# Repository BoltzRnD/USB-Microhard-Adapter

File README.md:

# USB-Microhard-Adapter
 USB to RS232 with 12V Boost Converter for Microhard

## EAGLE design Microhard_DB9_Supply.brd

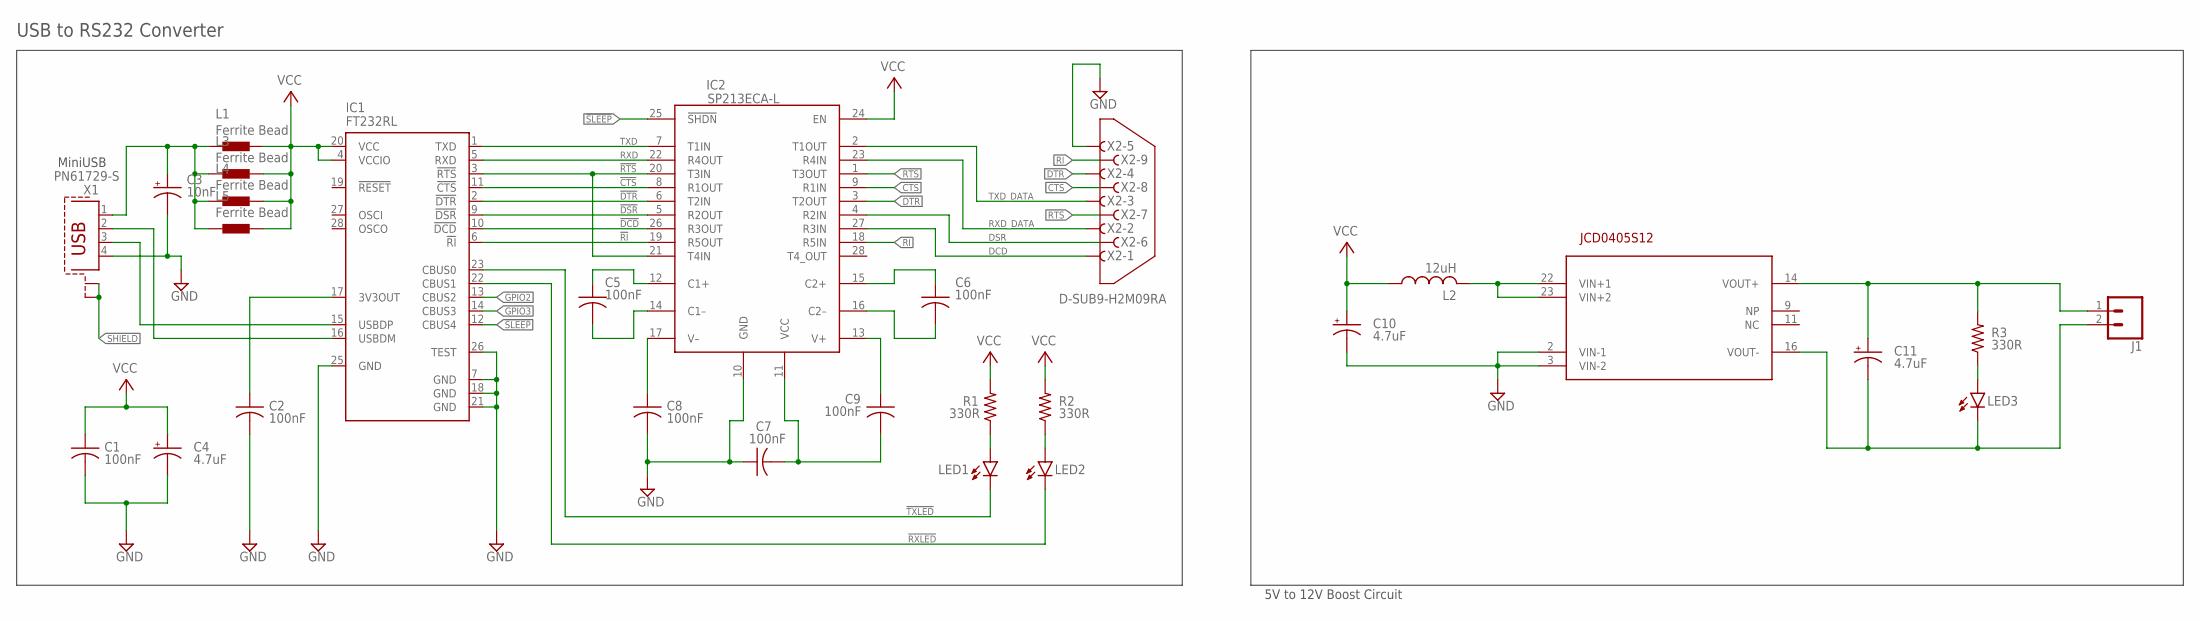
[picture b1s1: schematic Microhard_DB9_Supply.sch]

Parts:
C1, C2, C5, C6, C7, C8, C9: 100nF; C0402
C3: 10nF; PANASONIC_A
C4, C10, C11: 4.7uF; PANASONIC_D
IC1: FT232RL; SSOP28
IC2: SP213ECA-L; SSOP28
J1: CONN_02LOCK_LONGPADS; 1X02_LOCK_LONGPADS
L1, L3, L4, L5: Ferrite Bead; 0402
L2: 12uH; 0207/7
LED1, LED2, LED3: LEDCHIP-LED0603; CHIP-LED0603
R1, R2, R3: 330R; R0402
U$1: JCD0505S12JCD0505S12; DIP1524W53P254L3175H1040Q24A
X1: PN61729-S
X2: D-SUB9-H2M09RA; H2M09RA

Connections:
!CTS: IC1.11 (!CTS), IC2.8 (R1OUT)
!DCD: IC1.10 (!DCD), IC2.26 (R3OUT)
!DSR: IC1.9 (!DSR), IC2.5 (R2OUT)
!DTR: IC1.2 (!DTR), IC2.6 (T2IN)
!RI: IC1.6 (!RI), IC2.19 (R5OUT)
!RTS: IC1.3 (!RTS), IC2.20 (T3IN), IC2.21 (T4IN)
!RXLED: IC1.22 (CBUS1), LED2.C
!SLEEP: IC1.12 (CBUS4), IC2.25 (!SHDN)
!TXLED: IC1.23 (CBUS0), LED1.C
CTS: IC2.9 (R1IN), X2.8
DCD: IC2.27 (R3IN), X2.1
DSR: IC2.4 (R2IN), X2.6
DTR: IC2.3 (T2OUT), X2.4
GND: C1.2, C2.2, C3.-, C4.-, C7.1, C8.2, C10.-, IC1.7 (GND), IC1.18 (GND), IC1.21 (GND), IC1.25 (GND), IC1.26 (TEST), IC2.10 (GND), U$1.2 (VIN-1), U$1.3 (VIN-2), X1.4, X2.5
GPIO2: IC1.13 (CBUS2)
GPIO3: IC1.14 (CBUS3)
unnamed: C2.1, IC1.17 (3V3OUT)
unnamed: C3.+, L1.1, L3.1, L4.1, L5.1, X1.1
unnamed: L2.2, U$1.22 (VIN+1), U$1.23 (VIN+2)
unnamed: IC1.16 (USBDM), X1.2
unnamed: IC1.15 (USBDP), X1.3
unnamed: C11.+, J1.1, R3.2, U$1.14 (VOUT+)
unnamed: C11.-, J1.2, LED3.C, U$1.16 (VOUT-)
unnamed: LED3.A, R3.1
unnamed: LED1.A, R1.1
unnamed: LED2.A, R2.1
unnamed: C5.1, IC2.12 (C1+)
unnamed: C5.2, IC2.14 (C1–)
unnamed: C6.1, IC2.15 (C2+)
unnamed: C6.2, IC2.16 (C2–)
unnamed: C8.1, IC2.17 (V–)
unnamed: C7.2, C9.2, IC2.11 (VCC)
unnamed: C9.1, IC2.13 (V+)
RI: IC2.18 (R5IN), X2.9
RTS: IC2.1 (T3OUT), X2.7
RXD: IC1.5 (RXD), IC2.22 (R4OUT)
RXD_DATA: IC2.23 (R4IN), X2.2
SHIELD: X1.S1, X1.S2
TXD: IC1.1 (TXD), IC2.7 (T1IN)
TXD_DATA: IC2.2 (T1OUT), X2.3
VCC: C1.1, C4.+, C10.+, IC1.4 (VCCIO), IC1.20 (VCC), IC2.24 (EN), L1.2, L2.1, L3.2, L4.2, L5.2, R1.2, R2.2

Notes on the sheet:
USB to RS232 Converter
MiniUSB
5V to 12V Boost Circuit

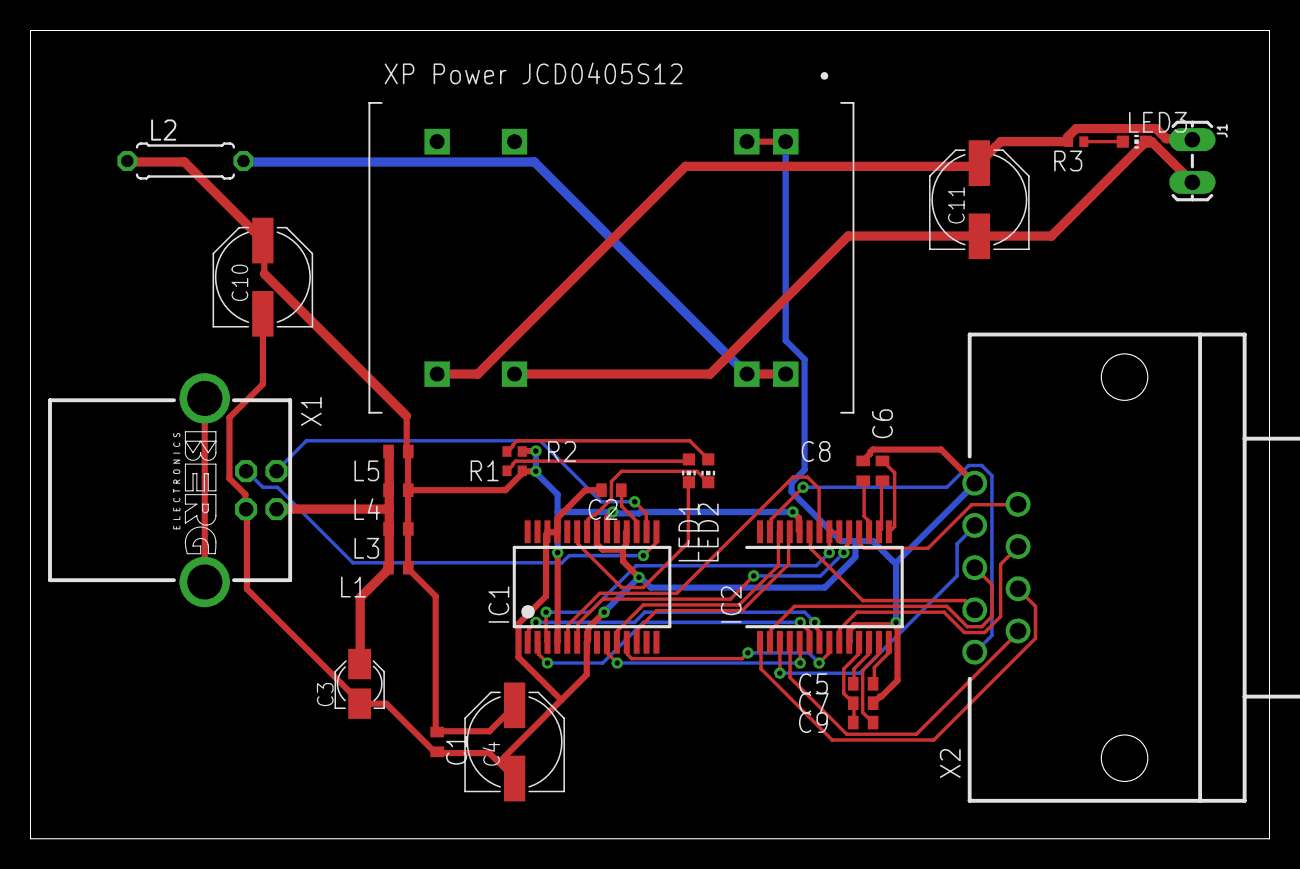
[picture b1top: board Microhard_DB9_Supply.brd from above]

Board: 2 copper layers, 81.3 x 53.0 mm, 28 parts (0 on the bottom side), 39 nets.

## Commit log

2019-12-11 added Board and updated Schematics

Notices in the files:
parts and their libraries:
SparkFun-Connectors: Licensing: Creative Commons ShareAlike 4.0 International - https://creativecommons.org/licenses/by-sa/4.0
